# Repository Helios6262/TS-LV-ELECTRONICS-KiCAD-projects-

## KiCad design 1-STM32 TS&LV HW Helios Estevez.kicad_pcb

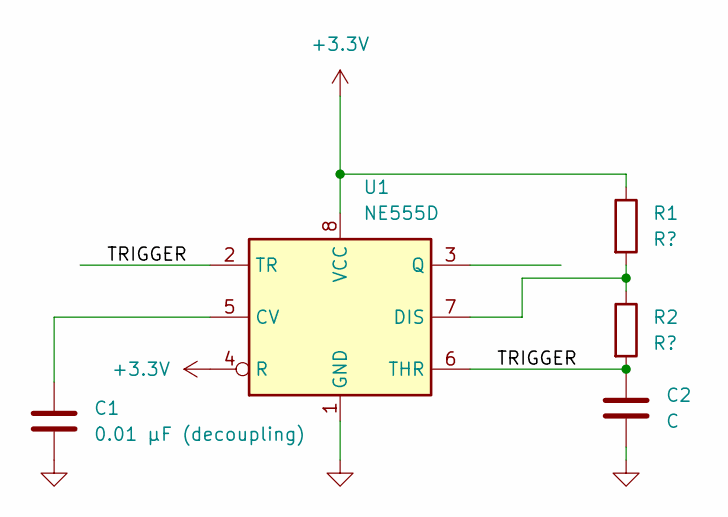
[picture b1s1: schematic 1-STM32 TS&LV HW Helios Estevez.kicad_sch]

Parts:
C1: 0.01 µF (decoupling); C_0603_1608Metric
C2: C; C_0603_1608Metric_Pad1.08x0.95mm_HandSolder
R1, R2: R?; R_0603_1608Metric_Pad0.98x0.95mm_HandSolder
U1: NE555D; SOIC-8_3.9x4.9mm_P1.27mm

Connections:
+3.3V: R1.1, U1.4 (R), U1.8 (VCC)
/TRIGGER: C2.1, R2.2, U1.2 (TR), U1.6 (THR)
GND: C1.2, C2.2, U1.1 (GND)
unnamed: C1.1, U1.5 (CV)
unnamed: R1.2, R2.1, U1.7 (DIS)

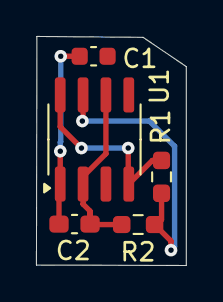
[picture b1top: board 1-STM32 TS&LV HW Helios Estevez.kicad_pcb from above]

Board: 2 copper layers, 8.3 x 12.7 mm, 5 parts (0 on the bottom side), 5 nets.

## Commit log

2024-09-24 Añadidos los archivos de la PCB
